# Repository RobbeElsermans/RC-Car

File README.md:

# RC-Car
code and files for my Tamiya Monster beetle

I'm refreshing my Tamiyan monster beetle with new 3D printed parts.
The transmitter is lost by the years so I'm making a new "experimental" one.

Sadly my gearbox broke (a couple of times with 3D printed gear. maybe I'll try carbon or even hard TPU for more durability) so I'm planning on redesigning the gearbox.

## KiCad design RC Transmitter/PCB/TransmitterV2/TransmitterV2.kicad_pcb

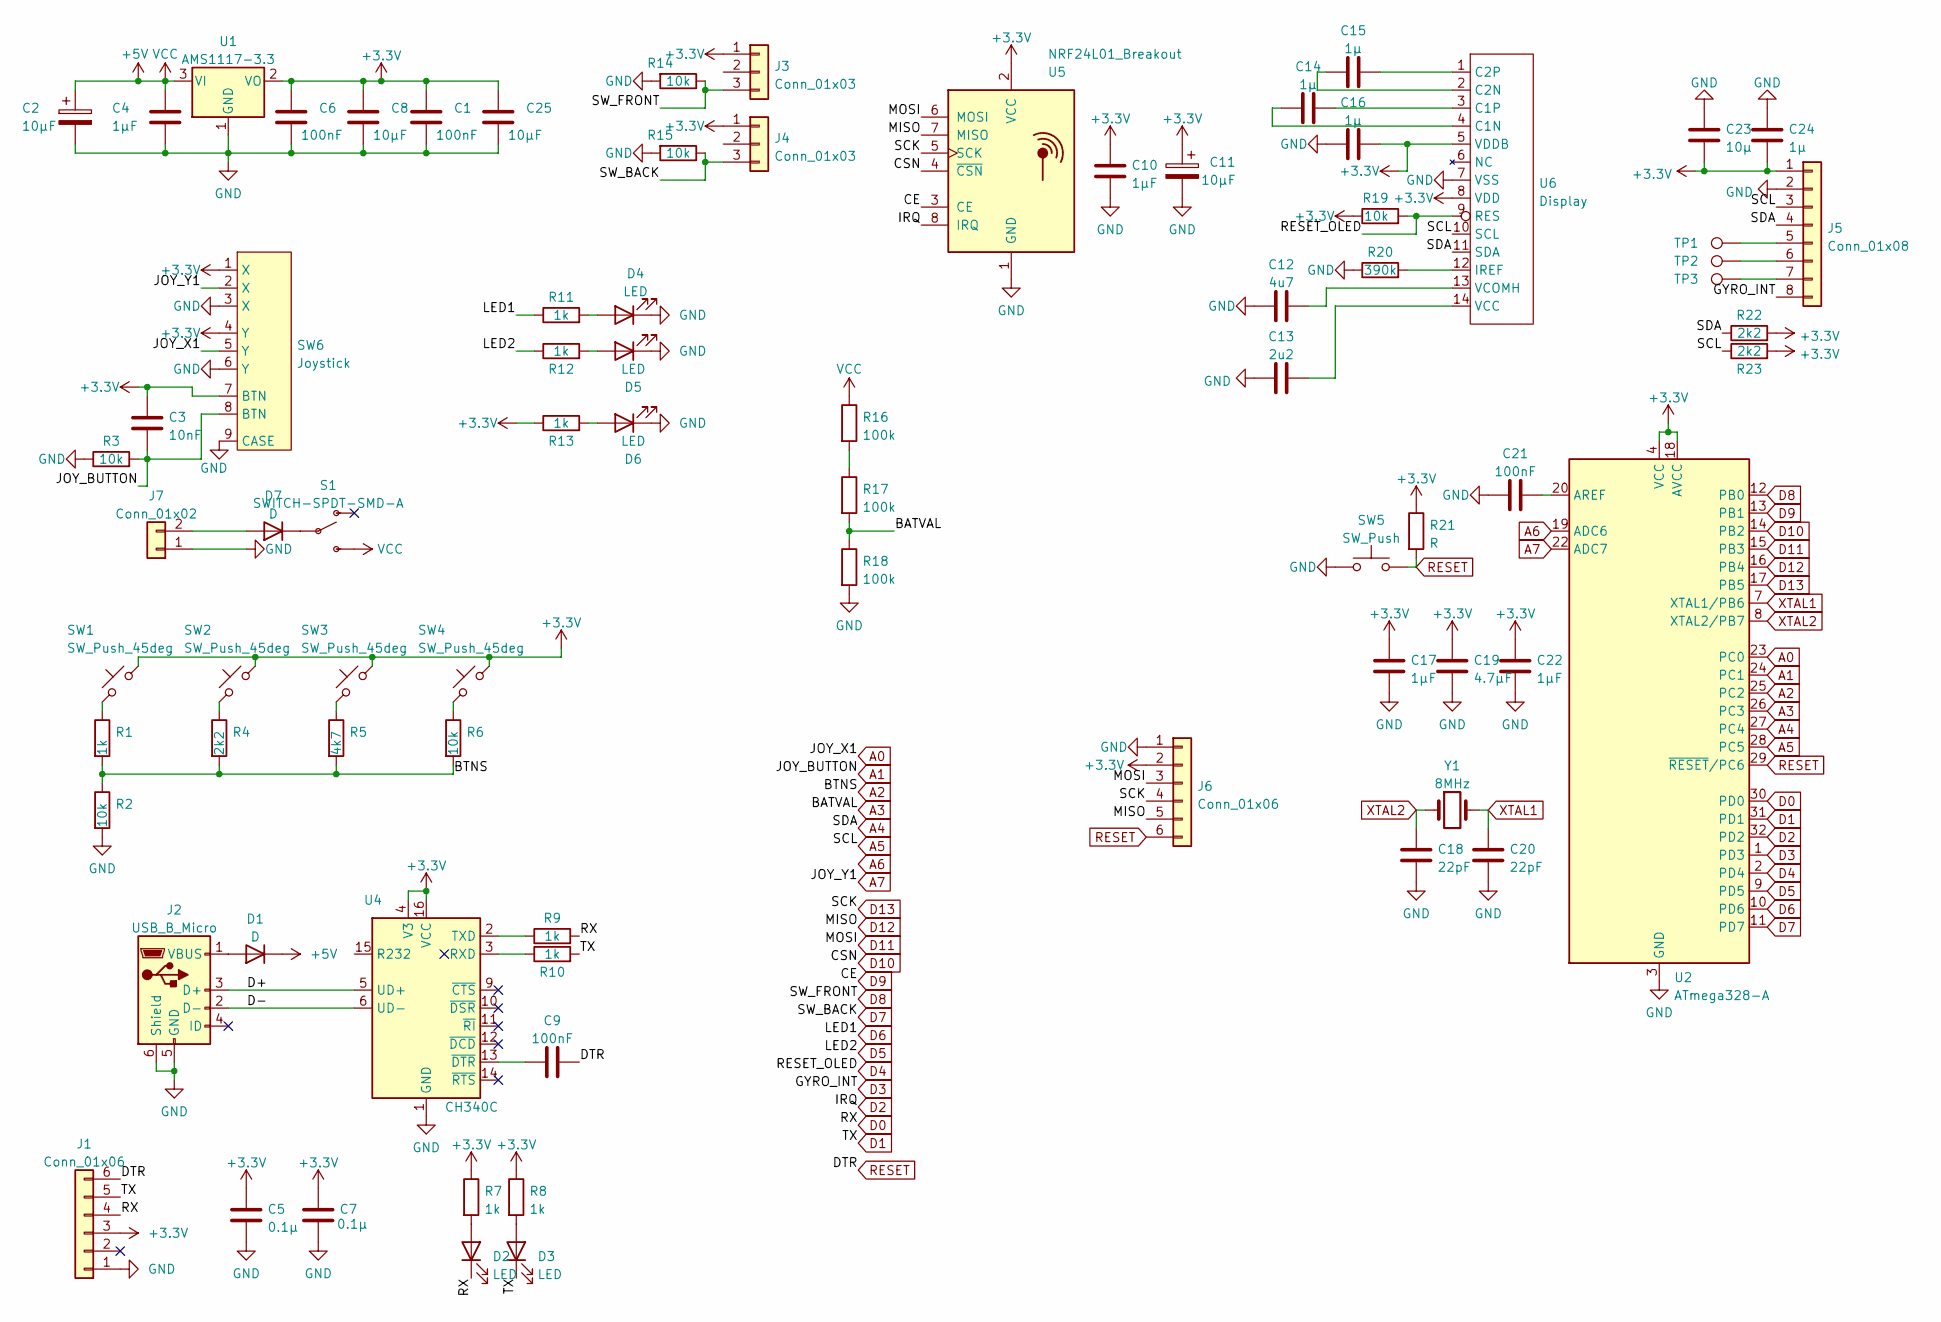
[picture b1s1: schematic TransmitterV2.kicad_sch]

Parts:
C1, C6, C9, C21: 100nF; C_0805_2012Metric
C2, C11: 10µF; CP_Radial_D6.3mm_P2.50mm
C3: 10nF; C_0805_2012Metric
C4, C10, C17, C22: 1µF; C_0805_2012Metric
C5, C7: 0.1µ; C_0805_2012Metric
C8, C25: 10µF; C_0805_2012Metric
C12: 4u7; C_0805_2012Metric_Pad1.18x1.45mm_HandSolder
C13: 2u2; C_0805_2012Metric_Pad1.18x1.45mm_HandSolder
C14, C15, C16, C24: 1µ; C_0805_2012Metric_Pad1.18x1.45mm_HandSolder
C18, C20: 22pF; C_0805_2012Metric
C19: 4.7µF; C_0805_2012Metric
C23: 10µ; C_0805_2012Metric_Pad1.18x1.45mm_HandSolder
D1, D7: D; D_DO-15_P10.16mm_Horizontal
D2, D3, D4, D5, D6: LED; LED_0805_2012Metric
J1: Conn_01x06; PinHeader_1x06_P2.54mm_Vertical
J2: USB_B_Micro; Connector micro usb B
J3, J4: Conn_01x03; Tacker
J5: Conn_01x08; PinHeader_1x08_P2.54mm_Vertical
J6: Conn_01x06; PinSocket_1x06_P2.54mm_Vertical
J7: Conn_01x02; JST_XH_B2B-XH-AM_1x02_P2.50mm_Vertical
R1, R7, R8, R9, R10, R11, R12, R13: 1k; R_0805_2012Metric
R2, R3, R6, R14, R15: 10k; R_0805_2012Metric
R4: 2k2; R_0805_2012Metric
R5: 4k7; R_0805_2012Metric
R16, R17, R18: 100k; R_0805_2012Metric
R19: 10k; R_0805_2012Metric_Pad1.20x1.40mm_HandSolder
R20: 390k; R_0805_2012Metric_Pad1.20x1.40mm_HandSolder
R21: R; R_0805_2012Metric
R22, R23: 2k2; R_0805_2012Metric_Pad1.20x1.40mm_HandSolder
S1: SWITCH-SPDT-SMD-A; SW_Slide_1P2T_CK_OS102011MS2Q
SW1, SW2, SW3, SW4: SW_Push_45deg; SW_SPST_CK_RS282G05A3
SW5: SW_Push; SW_SPST_CK_RS282G05A3
SW6: Joystick; JoyStick
TP1, TP2, TP3: TestPoint; TestPoint_Pad_D1.5mm
U1: AMS1117-3.3; SOT-223-3_TabPin2
U2: ATmega328-A; TQFP-32_7x7mm_P0.8mm
U4: CH340C; SOIC-16_3.9x9.9mm_P1.27mm
U5: NRF24L01_Breakout; nRF24L01_Breakout
U6: Display; KSWE 2832
Y1: 8MHz; Crystal_HC49-4H_Vertical

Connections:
+3V3: C1.1, C3.1, C5.2, C6.1, C7.2, C8.1, C10.1, C11.1, C16.2, C17.1, C19.1, C22.1, C23.2, C24.2, C25.1, J1.3, J3.1, J4.1, J5.1, J6.2, R7.1, R8.1, R13.1, R19.1, R21.1, R22.2, R23.2, SW1.2, SW2.2, SW3.2, SW4.2, SW6.1 (X), SW6.4 (Y), SW6.7 (BTN), U1.2 (VO), U2.4 (VCC), U2.6 (VCC), U2.18 (AVCC), U4.4 (V3), U4.16 (VCC), U5.2 (VCC), U6.5 (VDDB), U6.8 (VDD)
+5V: C2.1, C4.1, D1.1 (K), R16.1, S1.3 (S), U1.3 (VI)
/D+: J2.3 (D+), U4.5 (UD+)
/D-: J2.2 (D-), U4.6 (UD-)
A0: SW6.5 (Y), U2.23 (PC0)
A1: C3.2, R3.2, SW6.8 (BTN), U2.24 (PC1)
A2: R1.2, R2.1, R4.2, R5.2, R6.2, U2.25 (PC2)
A3: R17.2, R18.1, U2.26 (PC3)
A4: J5.4, R22.1, U2.27 (PC4), U6.11 (SDA)
A5: J5.3, R23.1, U2.28 (PC5), U6.10 (SCL)
A6: U2.19 (ADC6)
A7: SW6.2 (X), U2.22 (ADC7)
D0: D2.1 (K), J1.4, R9.2, U2.30 (PD0)
D1: D3.1 (K), J1.5, R10.2, U2.31 (PD1)
D2: U2.32 (PD2), U5.8 (IRQ)
D3: J5.8, U2.1 (PD3)
D4: R19.2, U2.2 (PD4), U6.9 (RES)
D5: R12.1, U2.9 (PD5)
D6: R11.1, U2.10 (PD6)
D7: J4.3, R15.1, U2.11 (PD7)
D8: J3.3, R14.1, U2.12 (PB0)
D9: U2.13 (PB1), U5.3 (CE)
D10: U2.14 (PB2), U5.4 (~CSN)
D11: J6.3, U2.15 (PB3), U5.6 (MOSI)
D12: J6.5, U2.16 (PB4), U5.7 (MISO)
D13: J6.4, U2.17 (PB5), U5.5 (SCK)
GND: C1.2, C2.2, C4.2, C5.1, C6.2, C7.1, C8.2, C10.2, C11.2, C12.1, C13.1, C16.1, C17.2, C18.2, C19.2, C20.2, C21.1, C22.2, C23.1, C24.1, C25.2, D4.1 (K), D5.1 (K), D6.1 (K), J1.1, J2.5 (GND), J2.6 (Shield), J5.2, J6.1, J7.1, R2.2, R3.1, R14.2, R15.2, R18.2, R20.1, SW5.1, SW6.3 (X), SW6.6 (Y), SW6.9 (CASE), U1.1 (GND), U2.3 (GND), U2.5 (GND), U2.21 (GND), U4.1 (GND), U5.1 (GND), U6.7 (VSS)
unnamed: C9.1, U4.13 (~DTR)
unnamed: C12.2, U6.13 (VCOMH)
unnamed: C13.2, U6.14 (VCC)
unnamed: C14.1, U6.4 (C1N)
unnamed: C14.2, U6.3 (C1P)
unnamed: C15.1, U6.2 (C2N)
unnamed: C15.2, U6.1 (C2P)
unnamed: C21.2, U2.20 (AREF)
unnamed: D1.2 (A), J2.1 (VBUS)
unnamed: D2.2 (A), R7.2
unnamed: D3.2 (A), R8.2
unnamed: D4.2 (A), R11.2
unnamed: D5.2 (A), R12.2
unnamed: D6.2 (A), R13.2
unnamed: D7.1 (K), S1.2
unnamed: D7.2 (A), J7.2
unnamed: J5.5, TP1.1
unnamed: J5.6, TP2.1
unnamed: J5.7, TP3.1
unnamed: R1.1, SW1.1
unnamed: R4.1, SW2.1
unnamed: R5.1, SW3.1
unnamed: R6.1, SW4.1
unnamed: R9.1, U4.2 (TXD)
unnamed: R10.1, U4.3 (RXD)
unnamed: R16.2, R17.1
unnamed: R20.2, U6.12 (IREF)
RESET: C9.2, J1.6, J6.6, R21.2, SW5.2, U2.29 (~RESET/PC6)
XTAL1: C20.1, U2.7 (XTAL1/PB6), Y1.2
XTAL2: C18.1, U2.8 (XTAL2/PB7), Y1.1

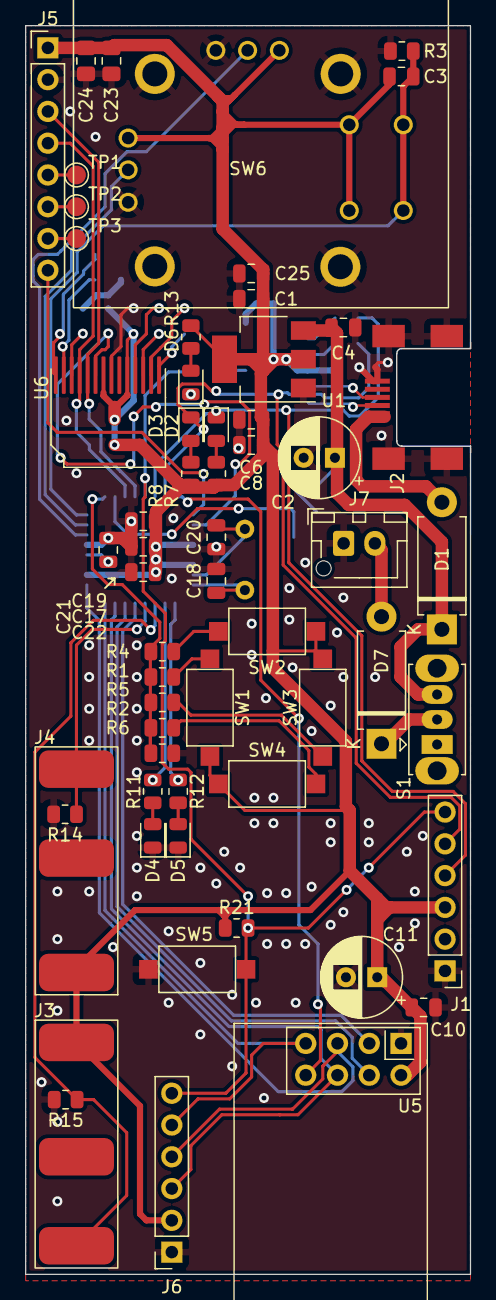
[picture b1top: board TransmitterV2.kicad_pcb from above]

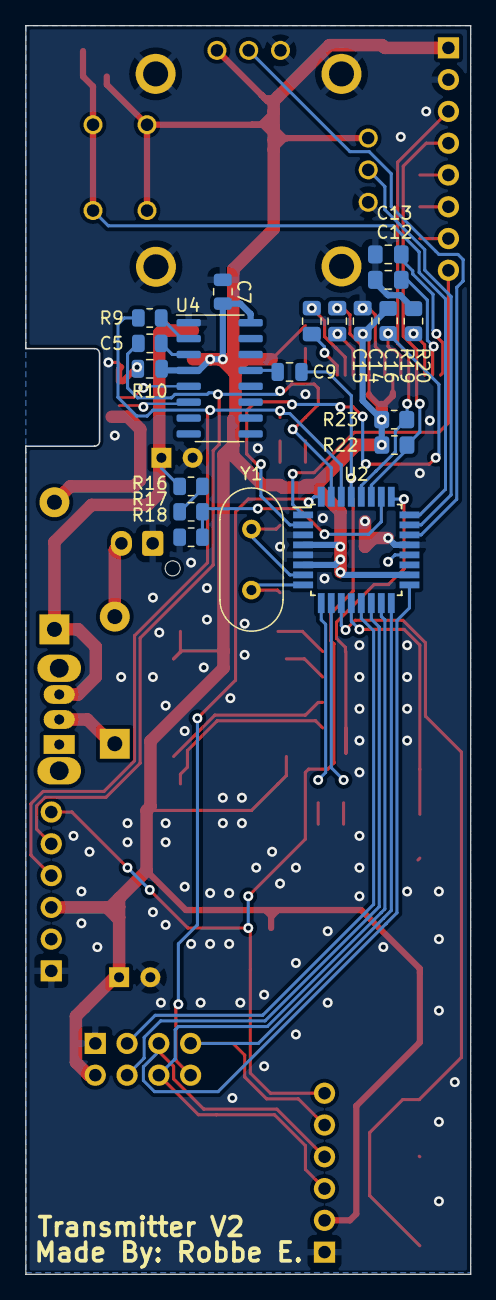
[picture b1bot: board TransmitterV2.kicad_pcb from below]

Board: 2 copper layers, 35.6 x 99.8 mm, 78 parts (20 on the bottom side), 56 nets.

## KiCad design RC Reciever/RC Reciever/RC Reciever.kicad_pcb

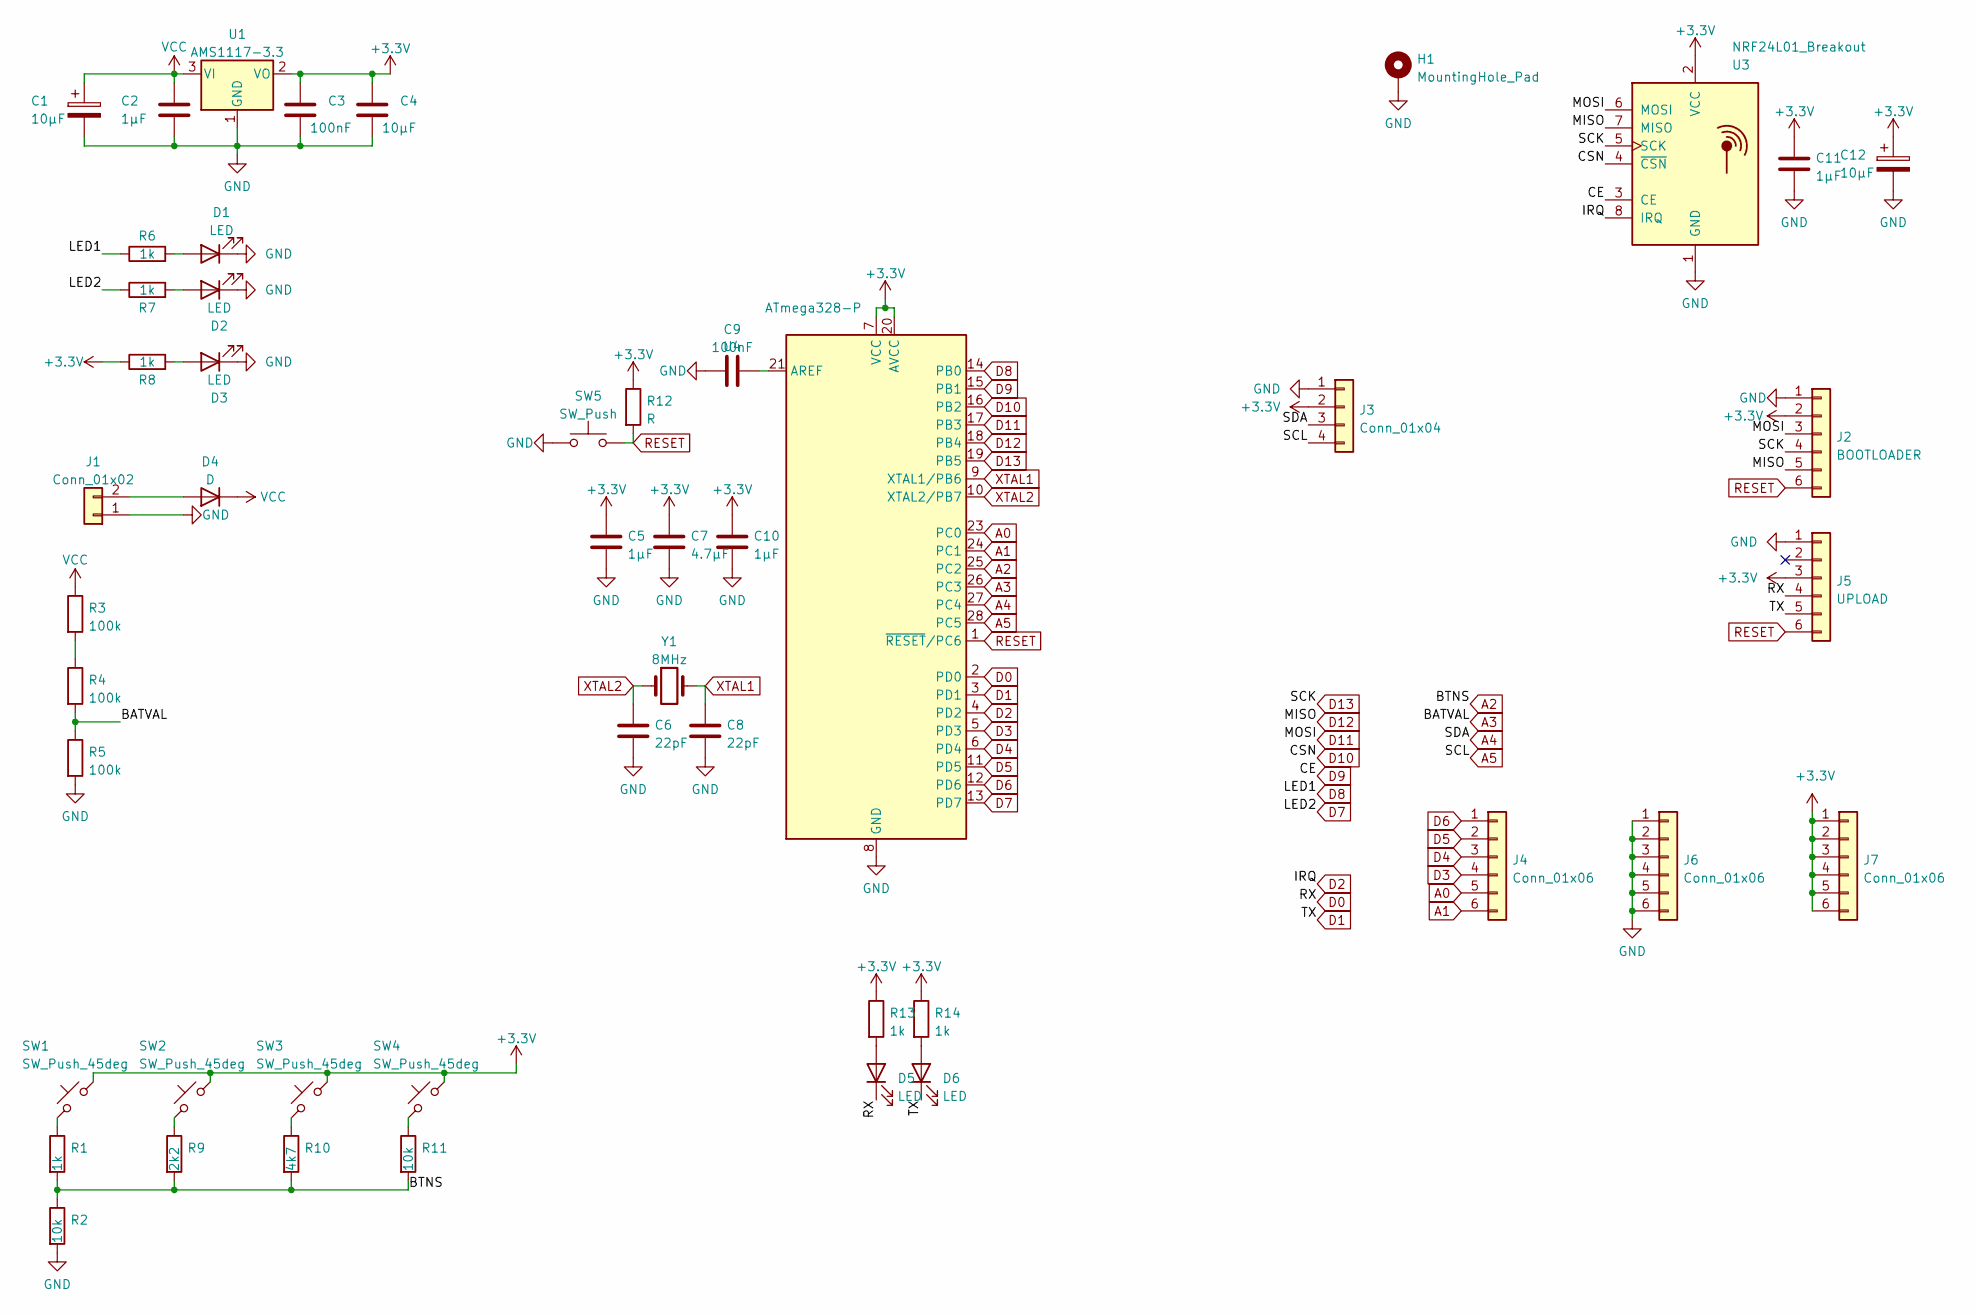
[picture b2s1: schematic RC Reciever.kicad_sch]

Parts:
C1, C12: 10µF; CP_Radial_D6.3mm_P2.50mm
C2, C5, C10, C11: 1µF; C_0805_2012Metric
C3, C9: 100nF; C_0805_2012Metric
C4: 10µF; C_0805_2012Metric
C6, C8: 22pF; C_0805_2012Metric
C7: 4.7µF; C_0805_2012Metric
D1, D2, D3, D5, D6: LED; LED_0805_2012Metric
D4: D; D_DO-15_P10.16mm_Horizontal
H1: MountingHole_Pad; MountingHole_2.2mm_M2_ISO7380_Pad_TopBottom
J1: Conn_01x02; TerminalBlock_Phoenix_MKDS-1,5-2-5.08_1x02_P5.08mm_Horizont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
J2: BOOTLOADER; PinSocket_1x06_P2.54mm_Vertical
J3: Conn_01x04; PinHeader_1x04_P2.54mm_Vertical
J4, J6, J7: Conn_01x06; PinHeader_1x06_P2.54mm_Vertical
J5: UPLOAD; PinHeader_1x06_P2.54mm_Vertical
R1, R6, R7, R8, R13, R14: 1k; R_0805_2012Metric
R2, R11: 10k; R_0805_2012Metric
R3, R4, R5: 100k; R_0805_2012Metric
R9: 2k2; R_0805_2012Metric
R10: 4k7; R_0805_2012Metric
R12: R; R_0805_2012Metric
SW1, SW2, SW3, SW4: SW_Push_45deg; SW_SPST_CK_RS282G05A3
SW5: SW_Push; SW_SPST_CK_RS282G05A3
U1: AMS1117-3.3; SOT-223-3_TabPin2
U3: NRF24L01_Breakout; nRF24L01_Breakout
U4: ATmega328-P; DIP-28_W7.62mm
Y1: 8MHz; Crystal_HC49-4H_Vertical

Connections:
+3V3: C3.1, C4.1, C5.1, C7.1, C10.1, C11.1, C12.1, J2.2, J3.2, J5.3, J7.1, J7.2, J7.3, J7.4, J7.5, J7.6, R8.1, R12.1, R13.1, R14.1, SW1.2, SW2.2, SW3.2, SW4.2, U1.2 (VO), U3.2 (VCC), U4.7 (VCC), U4.20 (AVCC)
A0: J4.5, U4.23 (PC0)
A1: J4.6, U4.24 (PC1)
A2: R1.2, R2.1, R9.2, R10.2, R11.2, U4.25 (PC2)
A3: R4.2, R5.1, U4.26 (PC3)
A4: J3.3, U4.27 (PC4)
A5: J3.4, U4.28 (PC5)
D0: D5.1 (K), J5.4, U4.2 (PD0)
D1: D6.1 (K), J5.5, U4.3 (PD1)
D2: U3.8 (IRQ), U4.4 (PD2)
D3: J4.4, U4.5 (PD3)
D4: J4.3, U4.6 (PD4)
D5: J4.2, U4.11 (PD5)
D6: J4.1, U4.12 (PD6)
D7: R7.1, U4.13 (PD7)
D8: R6.1, U4.14 (PB0)
D9: U3.3 (CE), U4.15 (PB1)
D10: U3.4 (~CSN), U4.16 (PB2)
D11: J2.3, U3.6 (MOSI), U4.17 (PB3)
D12: J2.5, U3.7 (MISO), U4.18 (PB4)
D13: J2.4, U3.5 (SCK), U4.19 (PB5)
GND: C1.2, C2.2, C3.2, C4.2, C5.2, C6.2, C7.2, C8.2, C9.1, C10.2, C11.2, C12.2, D1.1 (K), D2.1 (K), D3.1 (K), H1.1, J1.1, J2.1, J3.1, J5.1, J6.1, J6.2, J6.3, J6.4, J6.5, J6.6, R2.2, R5.2, SW5.1, U1.1 (GND), U3.1 (GND), U4.8 (GND), U4.22 (GND)
unnamed: C9.2, U4.21 (AREF)
unnamed: D1.2 (A), R6.2
unnamed: D2.2 (A), R7.2
unnamed: D3.2 (A), R8.2
unnamed: D4.2 (A), J1.2
unnamed: D5.2 (A), R13.2
unnamed: D6.2 (A), R14.2
unnamed: R1.1, SW1.1
unnamed: R3.2, R4.1
unnamed: R9.1, SW2.1
unnamed: R10.1, SW3.1
unnamed: R11.1, SW4.1
RESET: J2.6, J5.6, R12.2, SW5.2, U4.1 (~RESET/PC6)
VCC: C1.1, C2.1, D4.1 (K), R3.1, U1.3 (VI)
XTAL1: C8.1, U4.9 (XTAL1/PB6), Y1.2
XTAL2: C6.1, U4.10 (XTAL2/PB7), Y1.1

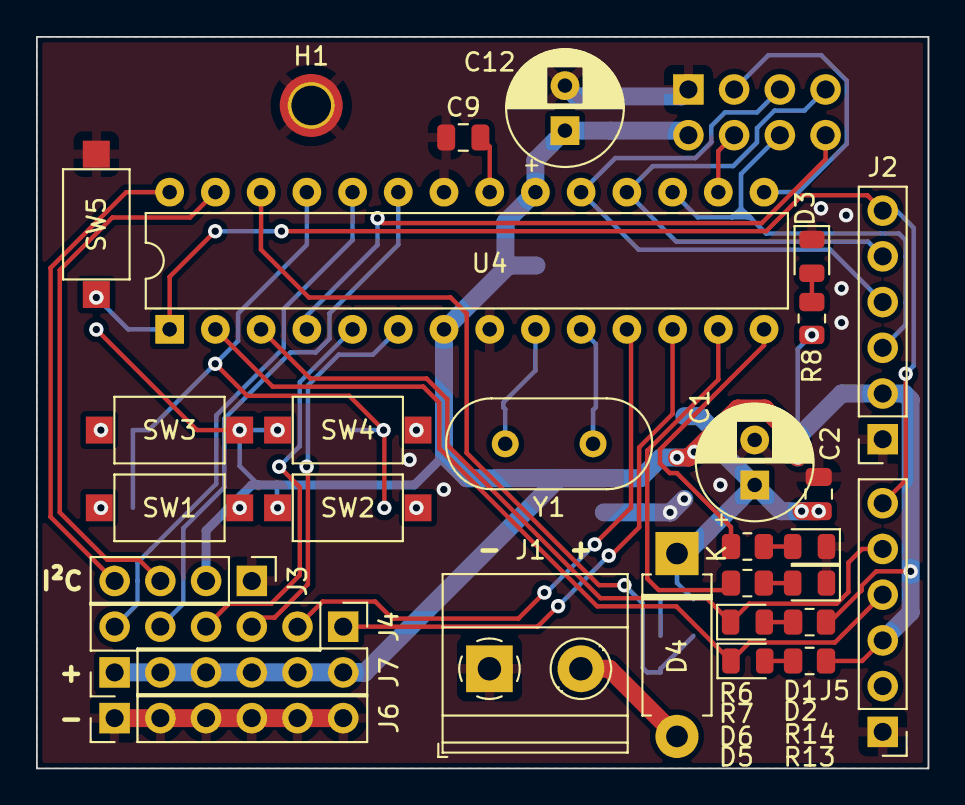
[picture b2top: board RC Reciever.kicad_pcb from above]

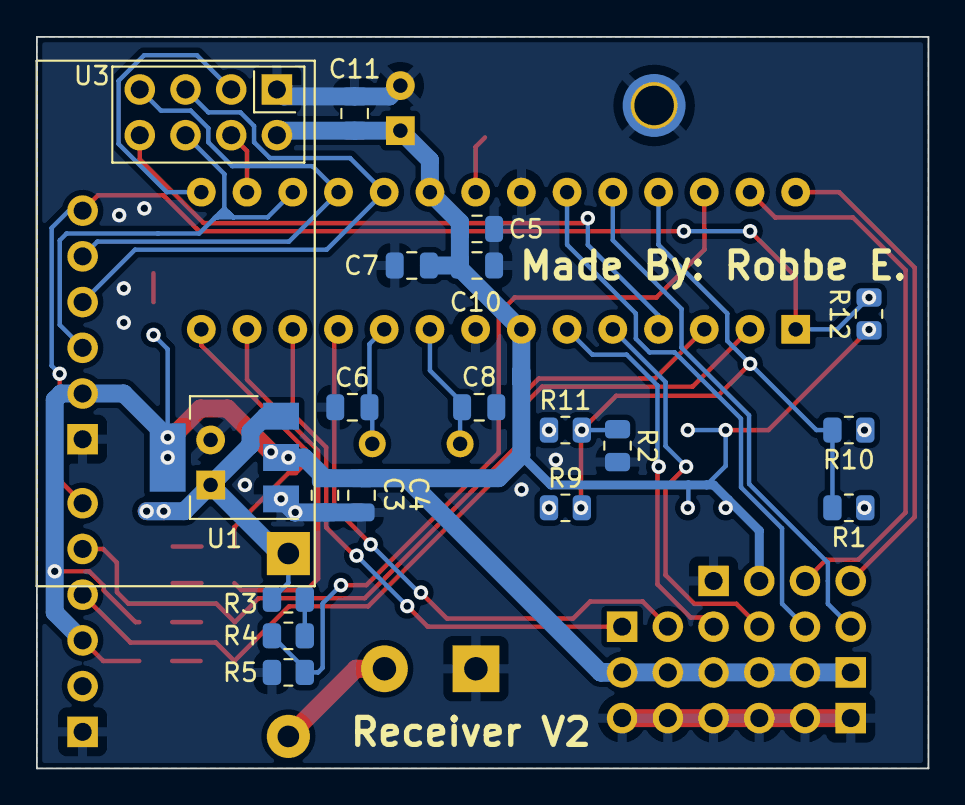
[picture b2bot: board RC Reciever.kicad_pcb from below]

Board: 2 copper layers, 49.5 x 40.6 mm, 49 parts (19 on the bottom side), 38 nets.

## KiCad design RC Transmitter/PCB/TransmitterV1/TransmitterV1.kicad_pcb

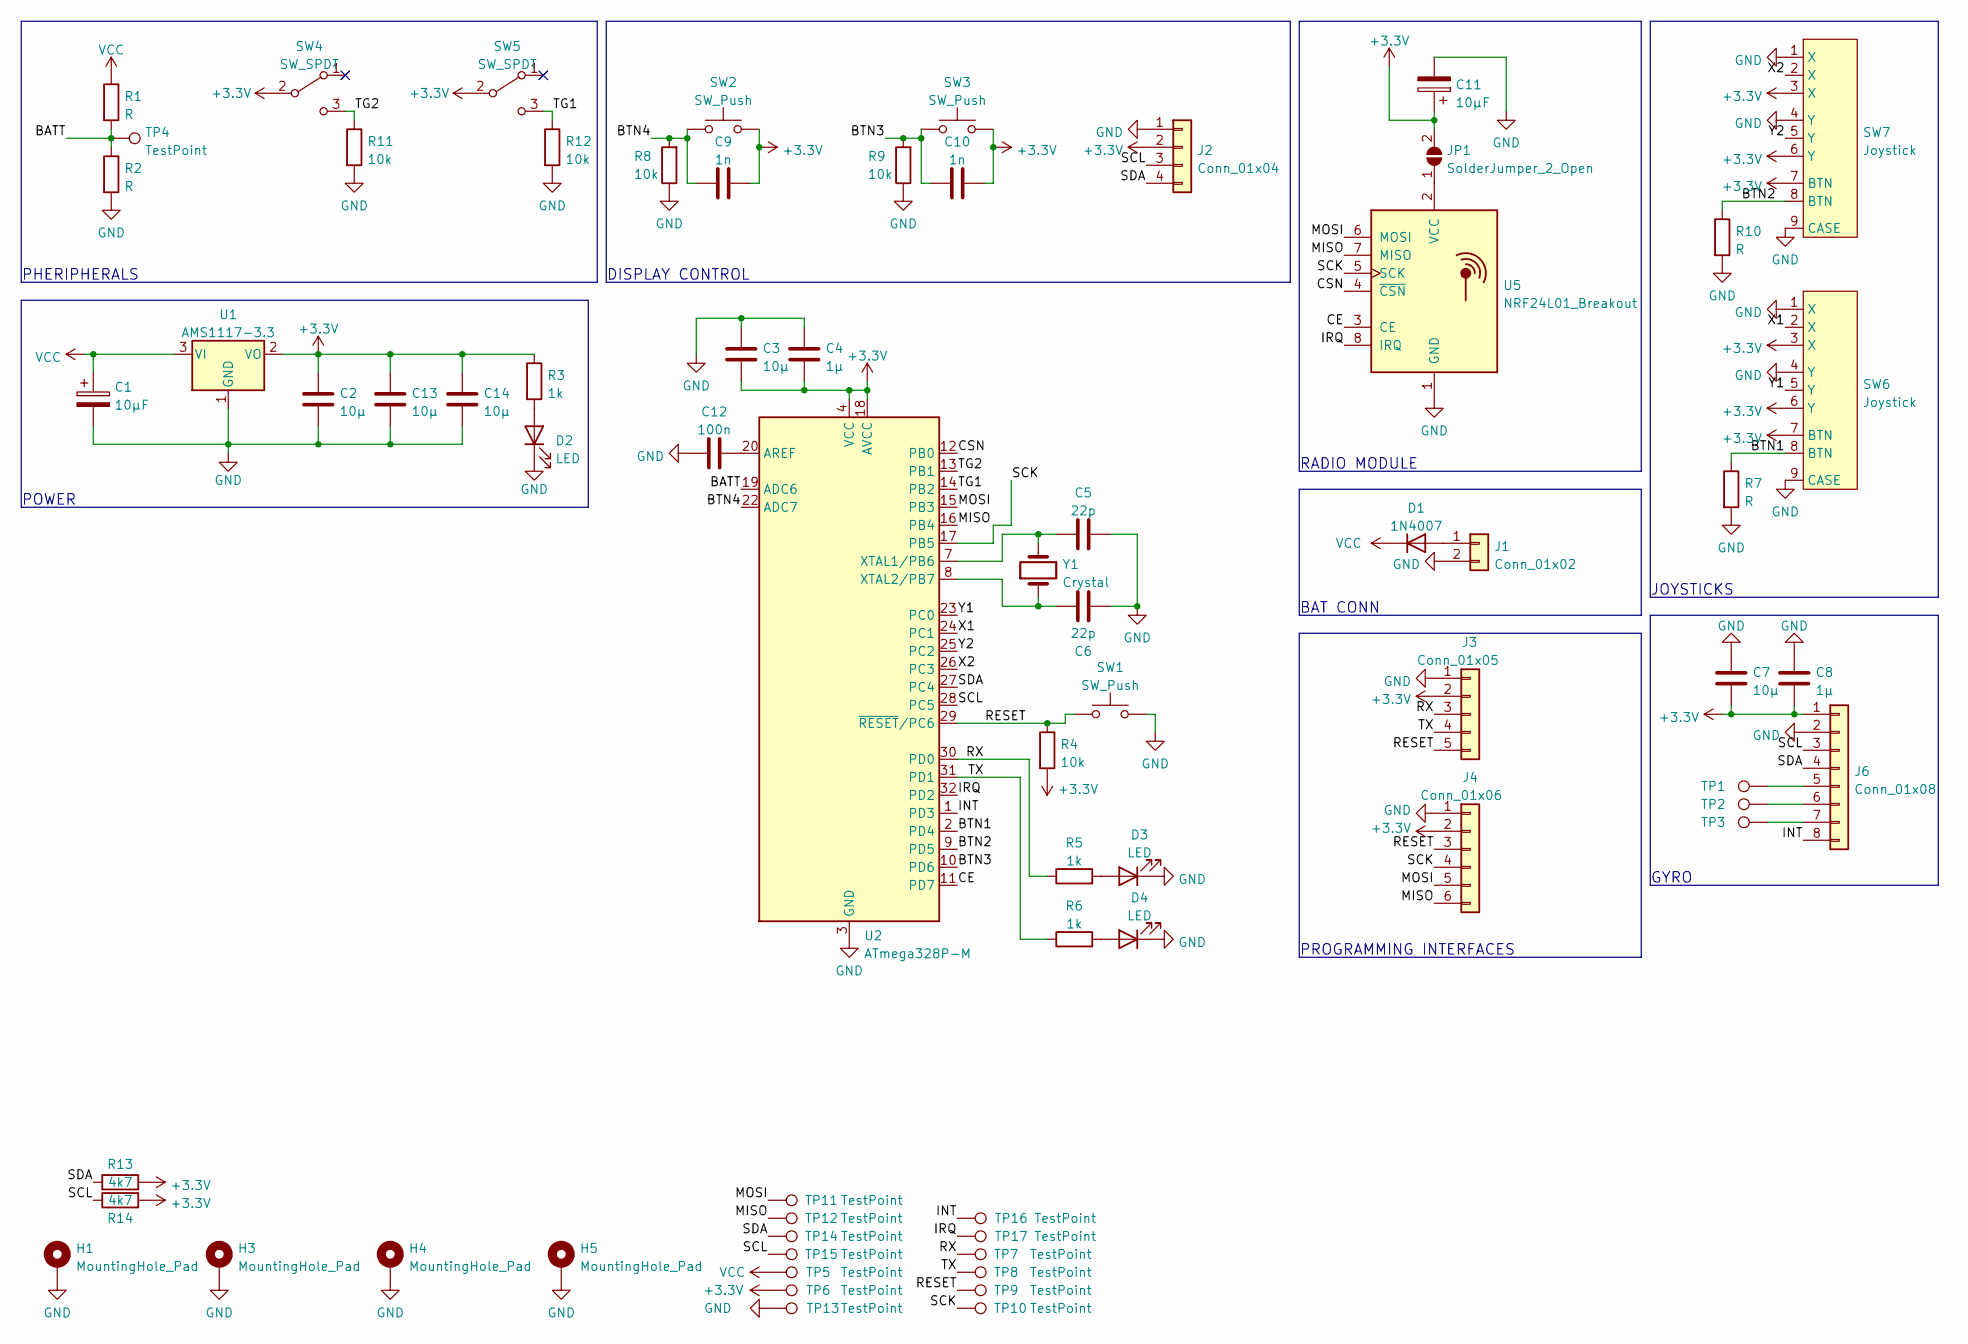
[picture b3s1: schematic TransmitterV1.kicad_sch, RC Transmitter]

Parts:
C1, C11: 10µF; CP_Radial_D6.3mm_P2.50mm
C2, C3, C7, C13, C14: 10µ; C_0805_2012Metric_Pad1.18x1.45mm_HandSolder
C4, C8: 1µ; C_0805_2012Metric_Pad1.18x1.45mm_HandSolder
C5, C6: 22p; C_0805_2012Metric_Pad1.18x1.45mm_HandSolder
C9, C10: 1n; C_0805_2012Metric_Pad1.18x1.45mm_HandSolder
C12: 100n; C_0805_2012Metric_Pad1.18x1.45mm_HandSolder
D1: 1N4007; D_5W_P10.16mm_Horizontal
D2, D3, D4: LED; LED_0805_2012Metric_Pad1.15x1.40mm_HandSolder
H1, H3, H4, H5: MountingHole_Pad; MountingHole_3.2mm_M3_Pad_Via
J1: Conn_01x02; PinHeader_1x02_P2.00mm_Vertical
J2: Conn_01x04; PinHeader_1x04_P2.54mm_Vertical
J3: Conn_01x05; PinHeader_1x05_P2.54mm_Vertical
J4: Conn_01x06; PinHeader_1x06_P2.54mm_Vertical
J6: Conn_01x08; PinHeader_1x08_P2.54mm_Vertical
JP1: SolderJumper_2_Open; SolderJumper-2_P1.3mm_Open_TrianglePad1.0x1.5mm
R1, R2, R7, R10: R; R_0805_2012Metric_Pad1.20x1.40mm_HandSolder
R3, R5, R6: 1k; R_0805_2012Metric_Pad1.20x1.40mm_HandSolder
R4, R8, R9, R11, R12: 10k; R_0805_2012Metric_Pad1.20x1.40mm_HandSolder
R13, R14: 4k7; R_0805_2012Metric_Pad1.20x1.40mm_HandSolder
SW1: SW_Push; SW_SPST_CK_RS282G05A3
SW2, SW3: SW_Push; SW_PUSH_6mm
SW4, SW5: SW_SPDT; Toggle_EdgeMount
SW6, SW7: Joystick; JoyStick
TP1, TP2, TP3: TestPoint; TestPoint_Pad_D1.5mm
TP4, TP5, TP6, TP7, TP8, TP9, TP10, TP11, TP12, TP13, TP14, TP15, TP16, TP17: TestPoint; TestPoint_THTPad_1.0x1.0mm_Drill0.5mm
U1: AMS1117-3.3; SOT-223-3_TabPin2
U2: ATmega328P-M; QFP80P900X900X120-32N
U5: NRF24L01_Breakout; nRF24L01_Breakout
Y1: Crystal; Crystal_HC49-4H_Vertical

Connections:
+3V3: C2.1, C3.2, C4.2, C7.2, C8.2, C9.2, C10.2, C11.1, C13.1, C14.1, J2.2, J3.2, J4.2, J6.1, JP1.2 (B), R3.1, R4.2, R13.2, R14.2, SW2.2, SW3.2, SW4.2 (B), SW5.2 (B), SW6.3 (X), SW6.6 (Y), SW6.7 (BTN), SW7.3 (X), SW7.6 (Y), SW7.7 (BTN), TP6.1, U1.2 (VO), U2.4 (VCC), U2.6 (VCC), U2.18 (AVCC)
/BATT: R1.2, R2.1, TP4.1, U2.19 (ADC6)
/BTN1: R7.1, SW6.8 (BTN), U2.2 (PD4)
/BTN2: R10.1, SW7.8 (BTN), U2.9 (PD5)
/BTN3: C10.1, R9.2, SW3.1, U2.10 (PD6)
/BTN4: C9.1, R8.2, SW2.1, U2.22 (ADC7)
/CE: U2.11 (PD7), U5.3 (CE)
/CSN: U2.12 (PB0), U5.4 (~CSN)
/INT: J6.8, TP16.1, U2.1 (PD3)
/IRQ: TP17.1, U2.32 (PD2), U5.8 (IRQ)
/MISO: J4.6, TP12.1, U2.16 (PB4), U5.7 (MISO)
/MOSI: J4.5, TP11.1, U2.15 (PB3), U5.6 (MOSI)
/RESET: J3.5, J4.3, R4.1, SW1.1, TP9.1, U2.29 (~RESET/PC6)
/RX: J3.3, R5.1, TP7.1, U2.30 (PD0)
/SCK: J4.4, TP10.1, U2.17 (PB5), U5.5 (SCK)
/SCL: J2.3, J6.3, R14.1, TP15.1, U2.28 (PC5)
/SDA: J2.4, J6.4, R13.1, TP14.1, U2.27 (PC4)
/TG1: R12.1, SW5.3 (C), U2.14 (PB2)
/TG2: R11.1, SW4.3 (C), U2.13 (PB1)
/TX: J3.4, R6.1, TP8.1, U2.31 (PD1)
/X1: SW6.2 (X), U2.24 (PC1)
/X2: SW7.2 (X), U2.26 (PC3)
/Y1: SW6.5 (Y), U2.23 (PC0)
/Y2: SW7.5 (Y), U2.25 (PC2)
GND: C1.2, C2.2, C3.1, C4.1, C5.2, C6.2, C7.1, C8.1, C11.2, C12.1, C13.2, C14.2, D2.1 (K), D3.1 (K), D4.1 (K), H1.1, H3.1, H4.1, H5.1, J1.2, J2.1, J3.1, J4.1, J6.2, R2.2, R7.2, R8.1, R9.1, R10.2, R11.2, R12.2, SW1.2, SW6.1 (X), SW6.4 (Y), SW6.9 (CASE), SW7.1 (X), SW7.4 (Y), SW7.9 (CASE), TP13.1, U1.1 (GND), U2.3 (GND), U2.5 (GND), U2.21 (GND), U2.33 (GND), U5.1 (GND)
unnamed: C5.1, U2.7 (XTAL1/PB6), Y1.2
unnamed: C6.1, U2.8 (XTAL2/PB7), Y1.1
unnamed: C12.2, U2.20 (AREF)
unnamed: D1.2 (A), J1.1
unnamed: D2.2 (A), R3.2
unnamed: D3.2 (A), R5.2
unnamed: D4.2 (A), R6.2
unnamed: J6.5, TP1.1
unnamed: J6.6, TP2.1
unnamed: J6.7, TP3.1
unnamed: JP1.1 (A), U5.2 (VCC)
VCC: C1.1, D1.1 (K), R1.1, TP5.1, U1.3 (VI)

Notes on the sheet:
PROGRAMMING INTERFACES
PHERIPHERALS
JOYSTICKS
GYRO
RADIO MODULE
BAT CONN
DISPLAY CONTROL
POWER

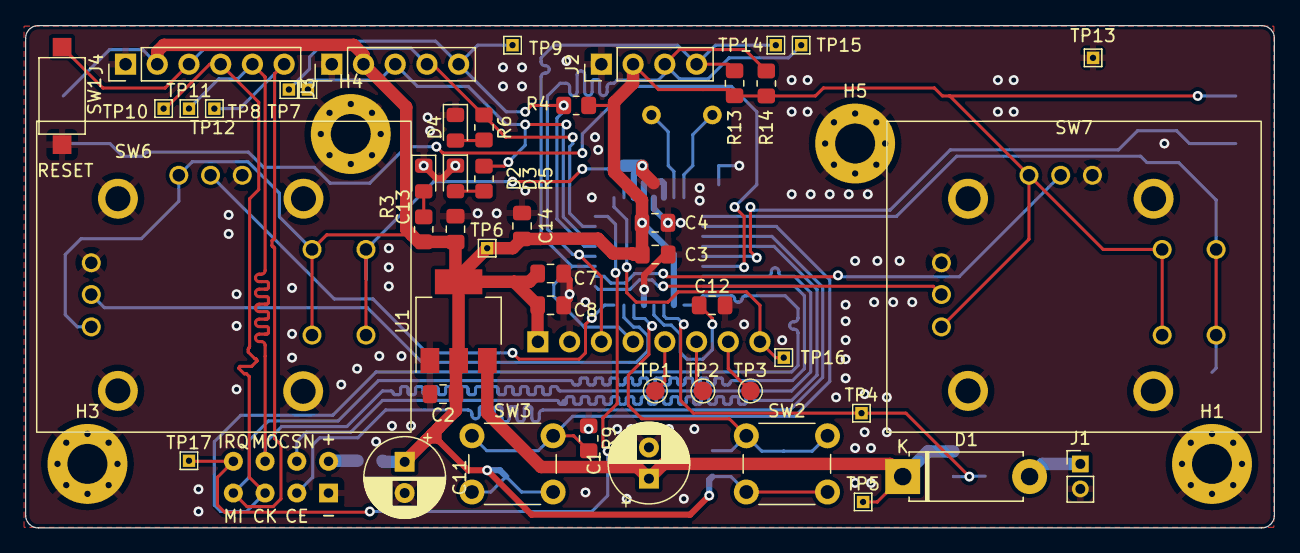
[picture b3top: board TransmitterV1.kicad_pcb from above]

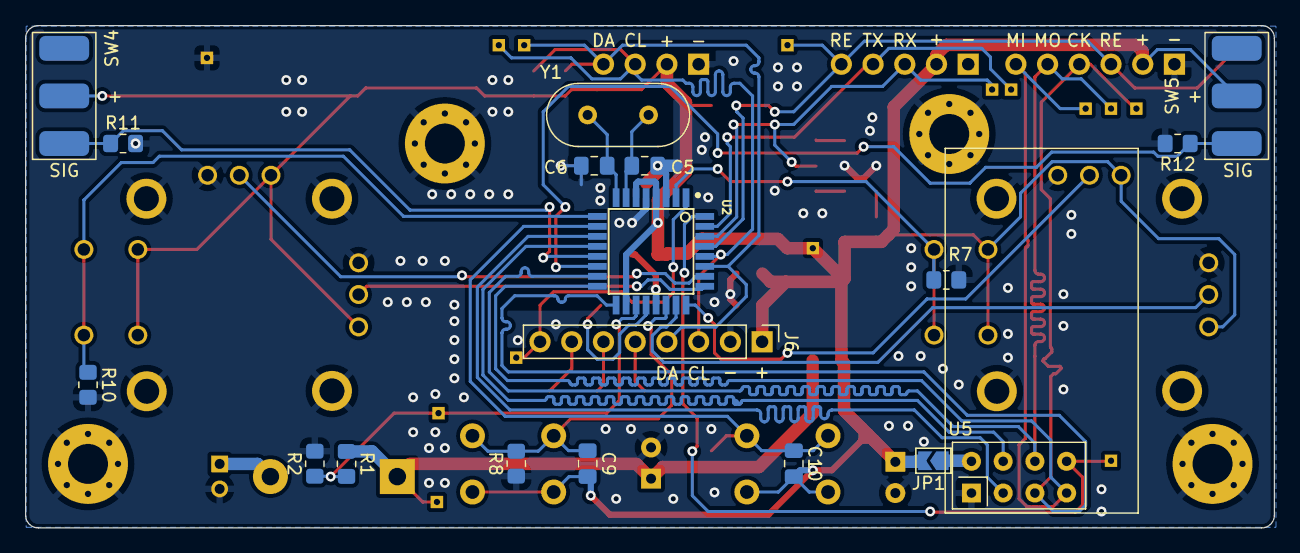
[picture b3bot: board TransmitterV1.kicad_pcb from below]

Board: 2 copper layers, 100.0 x 40.2 mm, 70 parts (18 on the bottom side), 37 nets.

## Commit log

2022-07-13 add main,debug screen + fallback receiver
2022-07-22 add 3D designs
2022-07-24 Add battery monitor
2022-08-27 Add RC Transmitter Case
2022-08-27 Add gcode rear bumper + pivot
2022-08-30 add Servo Saver
2022-08-30 edit gitignore
2022-08-31 Add correction page
2022-09-22 Add tandwiel met 0.3 nozzle
2023-05-28 Add begin replica
2023-06-25 add parts
